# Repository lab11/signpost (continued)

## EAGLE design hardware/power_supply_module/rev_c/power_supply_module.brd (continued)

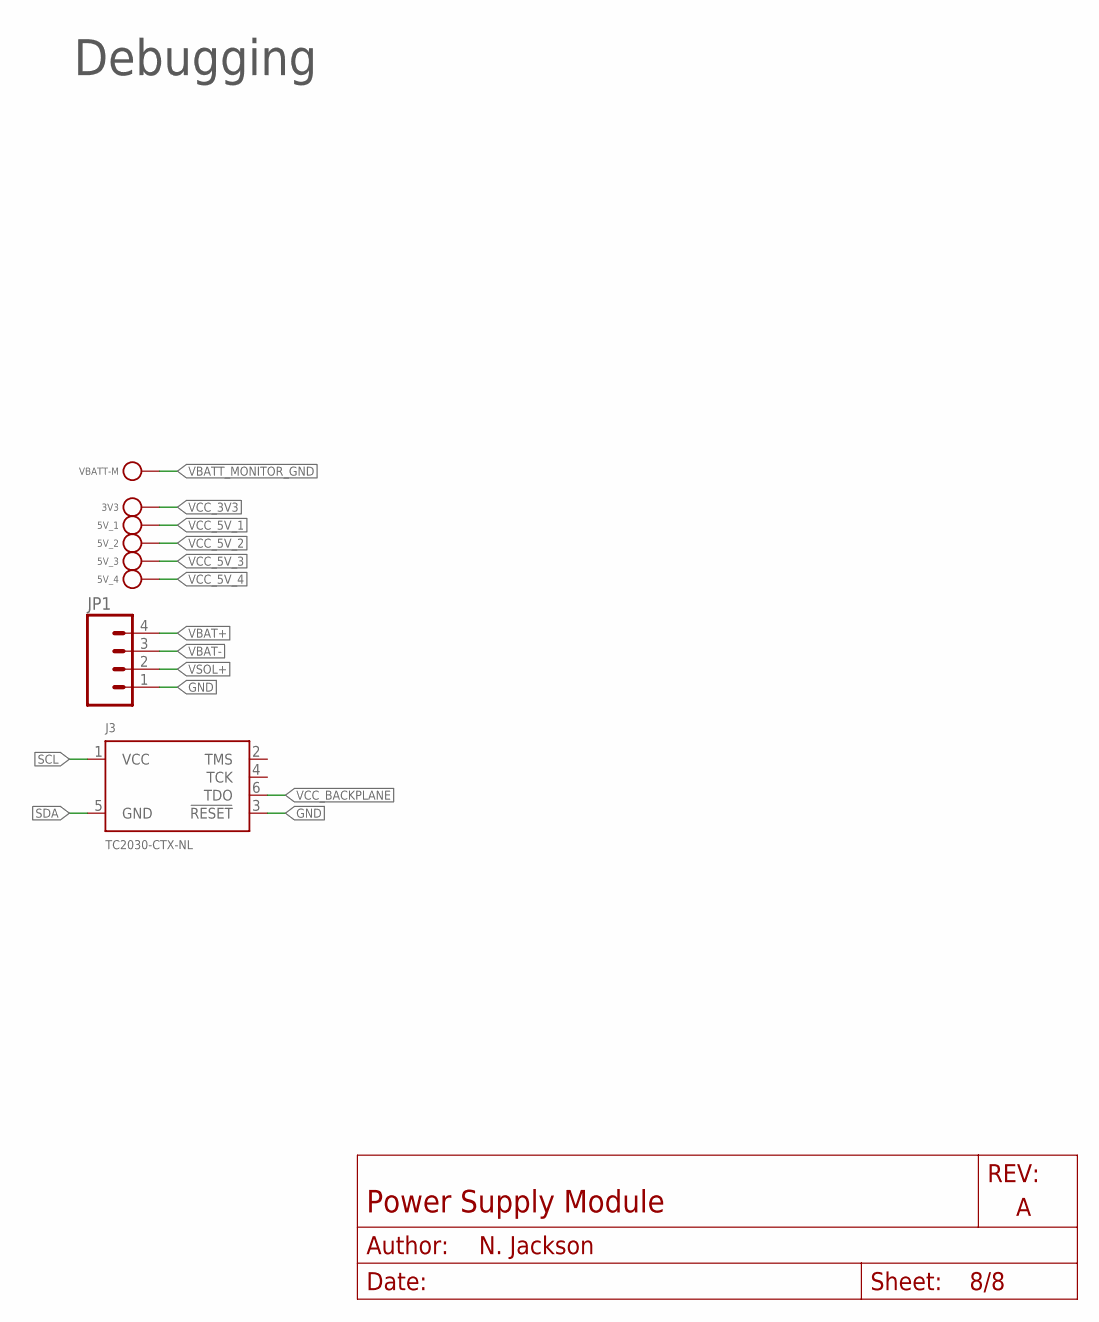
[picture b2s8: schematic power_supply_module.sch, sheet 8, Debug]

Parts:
3V3, 5V_1, 5V_2, 5V_3, 5V_4: TEST_POINT_0.040IN; TESTPOINT_0.040IN
J3: TC2030-CTX-NL; TC2030-IDC-NL
JP1: M04PTH; 1X04
VBATT-M: TEST_POINT_0.040IN; TESTPOINT_0.040IN

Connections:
GND: J3.3 (!RESET), JP1.1; also elsewhere on the board
SCL: J3.1 (VCC); also elsewhere on the board
SDA: J3.5 (GND); also elsewhere on the board
VBAT+: JP1.4; also elsewhere on the board
VBAT-: JP1.3; also elsewhere on the board
VBATT_MONITOR_GND: VBATT-M.TESTPOINT; also elsewhere on the board
VCC_3V3: 3V3.TESTPOINT; also elsewhere on the board
VCC_5V_1: 5V_1.TESTPOINT; also elsewhere on the board
VCC_5V_2: 5V_2.TESTPOINT; also elsewhere on the board
VCC_5V_3: 5V_3.TESTPOINT; also elsewhere on the board
VCC_5V_4: 5V_4.TESTPOINT; also elsewhere on the board
VCC_BACKPLANE: J3.6 (TDO); also elsewhere on the board
VSOL+: JP1.2; also elsewhere on the board

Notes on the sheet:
Debugging

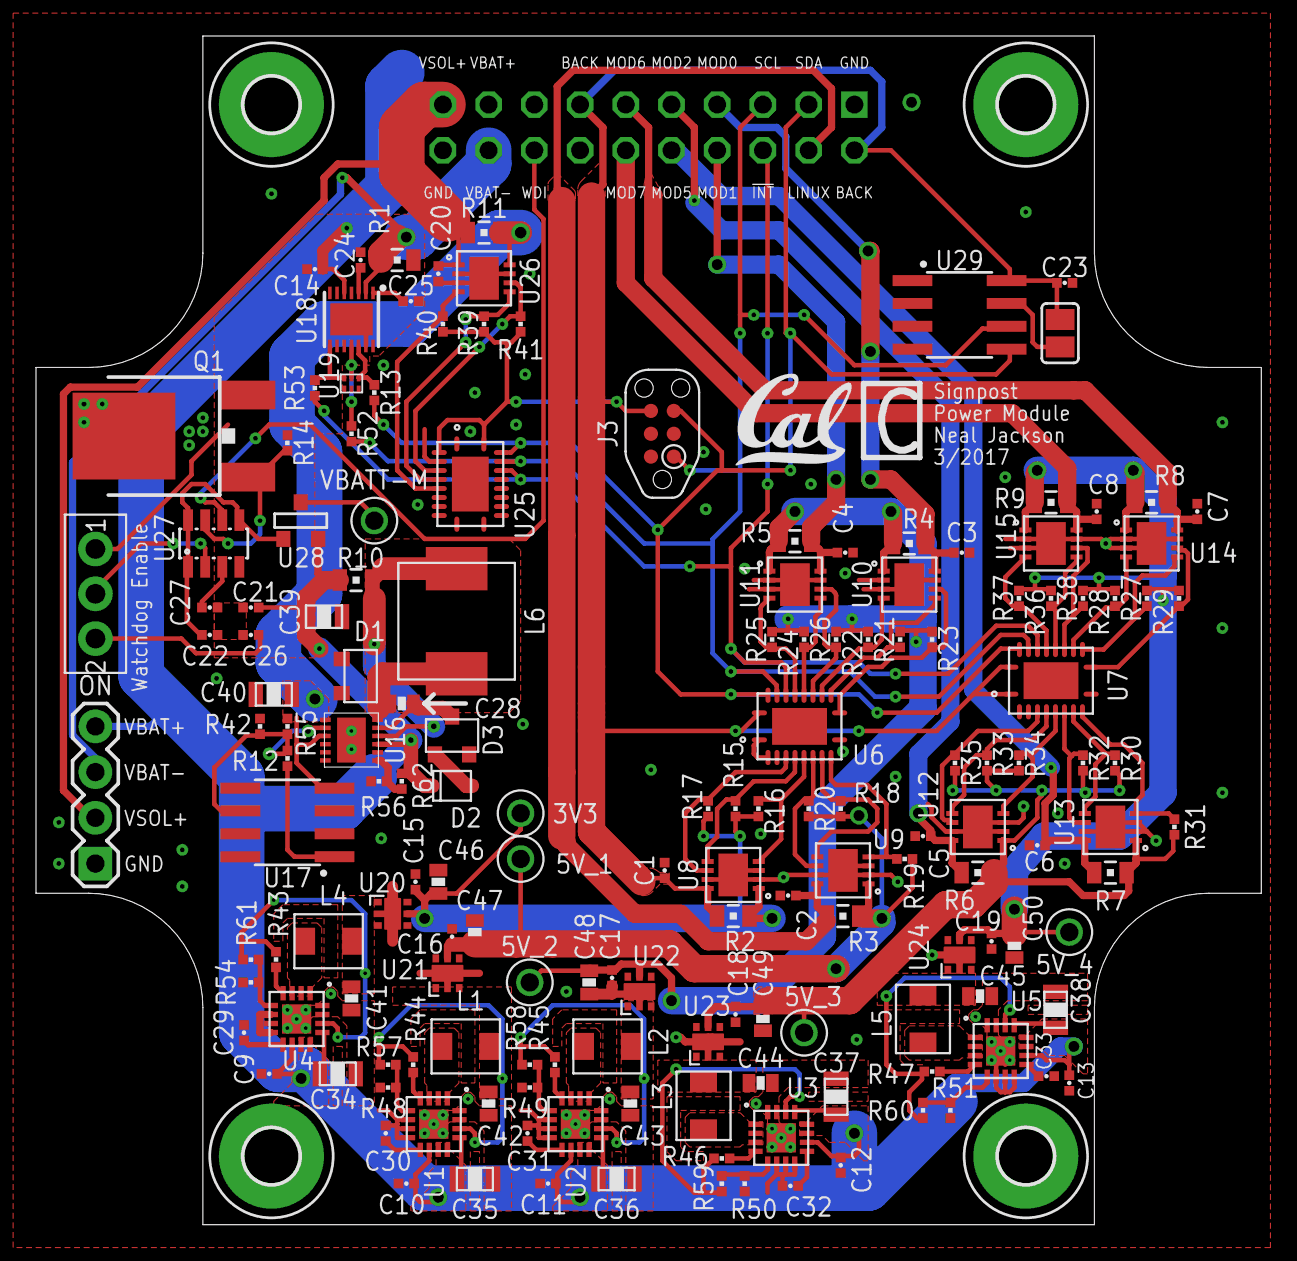
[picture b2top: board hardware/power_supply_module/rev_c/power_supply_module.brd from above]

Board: 2 copper layers, 68.1 x 66.0 mm, 167 parts (0 on the bottom side), 93 nets.

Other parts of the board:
U$1: UCB_CAL_200MIL

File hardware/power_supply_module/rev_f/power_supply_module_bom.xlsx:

Qty | Value | Device | Package | Parts | Description | DESCRIPTION | DIGIKEY | MANUFACTURER | MOUSER | MPN
1 |  | DIODE_SCHOTTKYSOD323 | SOD323 | D3 |  | DIODE SCHOTTKY 40V 200MA SOD323 | CMDSH2-4L CT-ND | Central Semiconductor |  | CMDSH2-4L TR
1 | 0.010 Ω | RESISTOR0805_RES | 0805_RES | R1 | Resistor | RES SMD 0.01 OHM 1% 1/2W 0805 | WSLPB-.01CT-ND | Vishay Dale |  | WSLP0805R0100FEB
8 | 0.017 Ω | RESISTOR0805_RES | 0805_RES | R2, R3, R4, R5, R6, R7, R8, R9 | Resistor | RES SMD 0.017 OHM 1% 1/2W 0805 | WSLPB-.017CT-ND | Vishay Dale |  | WSLP0805R0170FEB
2 | 0.05 Ω | RESISTOR0805_RES | 0805_RES | R10, R11 | Resistor | RES SMD 0.05 OHM 1% 1/2W 0805 | WSLPB-.05CT-ND | Vishay Dale |  | WSLP0805R0500FEB
23 | 0.1 uF | CAPACITOR0402_CAP | 0402_CAP | C1, C2, C3, C4, C5, C6, C7, C8, C9, C10, C11, C12, C13, C14, C15, C16, C17, C18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 | SMD Capacitor | CAP CER 0.1UF 25V X5R 0402 | 490-5920-1-ND | Murata |  | GRM155R61E104KA87D
3 | 0.47 uF | CAPACITOR0402_CAP | 0402_CAP | C24, C25, C26 | SMD Capacitor | CAP CER 0.47UF 6.3V X5R 0402 | 490-3266-1-ND | Murata |  | GRM155R60J474KE19D
1 | 0.82 uF | CAPACITOR0402_CAP | 0402_CAP | C27 | SMD Capacitor | CAP CER 0.82UF 6.3V X6S 0402 | 490-10440-1-ND | Murata |  | GRM155C80J824KE15D
2 | 1 MΩ | RESISTOR0402_RES | 0402_RES | R15, R16 | Resistor | RES SMD 1M OHM 1% 1/10W 0402 | P1.00MLCT-ND | Panasonic |  | ERJ-2RKF1004X
3 | 1 kΩ | RESISTOR0402_RES | 0402_RES | R12, R13, R66 | Resistor | RES SMD 1K OHM 5% 1/10W 0402 | P1.0KJCT-ND | Panasonic |  | ERJ-2GEJ102X
1 | 1 uF | CAPACITOR0603_CAP | 0603_CAP | C28 | SMD Capacitor | CAP CER 1UF 10V X5R 0603 | 490-1543-1-ND | Murata |  | GRM188R61A105KA61D
7 | 10 uF | CAPACITOR0805_CAP | 0805_CAP | C34, C35, C36, C37, C38, C39, C40 | SMD Capacitor | CAP CER 10UF 25V 10% X5R 0805 | 490-5523-1-ND | Murata |  | GRM21BR61E106KA73L
5 | 100 kΩ | RESISTOR0402_RES | 0402_RES | R45, R46, R47, R48, R49 | Resistor | RES SMD 100K OHM 5% 1/10W 0402 | P100KJCT-ND | Panasonic |  | ERJ-2GEJ104X
4 | 130 kΩ | RESISTOR0402_RES | 0402_RES | R50, R51, R52, R53 | Resistor | RES SMD 130K OHM 1% 1/10W 0402 | P130KLCT-ND | Panasonic |  | ERJ-2RKF1303X
3 | 150 Ω | RESISTOR0402_RES | 0402_RES | R54, R55, R70 | Resistor | RES SMD 150 OHM 1% 1/10W 0402 | P150LCT-ND | Panasonic |  | ERJ-2RKF1500X
27 | 2 kΩ | RESISTOR0402_RES | 0402_RES | R17, R18, R19, R20, R21, R22, R23, R24, R25, R26, R27, R28, R29, R30, R31, R32,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 | Resistor | RES SMD 2K OHM 1% 1/10W 0402 | P2.00KLCT-ND | Panasonic |  | ERJ-2RKF2001X
5 | 2.2 uH | INDUCTORIHL | IHL-1212BZ-11 | L1, L2, L3, L4, L5 | A very specific inductor |  | 541-1322-1-ND | Vishay Dale |  | IHLP1212BZER2R2M11
10 | 22 uF | CAPACITOR0603_CAP | 0603_CAP | C41, C42, C43, C44, C45, C46, C47, C48, C49, C50 | SMD Capacitor | CAP CER 22UF 6.3V X5R 0603 | 1276-1193-1-ND | Samsung |  | CL10A226MQ8NRNC
1 | 23.2 kΩ | RESISTOR0805_RES | 0805_RES | R44 | Resistor | RES SMD 23.2K OHM 0.1% 1/8W 0805 | P23.2KDACT-ND | Panasonic |  | ERA6AEB2322V
1 | 240 kΩ | RESISTOR0402_RES | 0402_RES | R56 | Resistor | RES SMD 240K OHM 1% 1/10W 0402 | P240KLCT-ND | Panasonic |  | ERJ-2RKF2403X
5 | 3.3 nF | CAPACITOR0402_CAP | 0402_CAP | C29, C30, C31, C32, C33 | SMD Capacitor | CAP CER 3300PF 50V 10% X7R 0402 | 490-3248-1-ND | Murata |  | GRM155R71H332KA01D
1 | 3.3V | TILM34803.3V | SOT-23 | U28 | Very simple LDO 100ma 3v3 | IC REG LDO 3.3V 50MA SOT23-3 | ZMR330FCT-ND | Diodes Inc. |  | ZMR330FTA
1 | 301 kΩ | RESISTOR0805_RES | 0805_RES | R57 | Resistor | RES SMD 301K OHM 0.1% 1/8W 0805 | P301KDACT-ND | Panasonic |  | ERA-6AEB3013V
1 | 340 kΩ | RESISTOR0805_RES | 0805_RES | R58 | Resistor | RES SMD 340K OHM 0.1% 1/8W 0805 | P340KDACT-ND | Panasonic |  | ERA-6AEB3403V
1 | 6.8uH | INDUCTORIHL2525CZ | IHL-2525CZ | L6 | A very specific inductor | FIXED IND 6.8UH 5.5A 46.8 MOHM | 541-2582-1-ND | Vishay Dale |  | IHLP2525CZER6R8M11
4 | 680 kΩ | RESISTOR0402_RES | 0402_RES | R59, R60, R61, R62 | Resistor | RES SMD 680K OHM 1% 1/10W 0402 | P680KLCT-ND | Panasonic |  | ERJ-2RKF6803X
1 | 750 kΩ | RESISTOR0402_RES | 0402_RES | R63 | Resistor | RES SMD 750K OHM 5% 1/10W 0402 | P750KJCT-ND | Panasonic |  | ERJ-2GEJ754X
1 | 953 kΩ | RESISTOR0805_RES | 0805_RES | R64 | Resistor | RES SMD 953K OHM 0.1% 1/8W 0805 | P953KDACT-ND | Panasonic |  | ERA-6AEB9533V
5 | AP22814 | AP22814 | U-DFN2020-6 | U20, U21, U22, U23, U24 | SINGLE CHANNEL POWER DISTRIBUTION LOAD SWITCH |  | AP22814ASN-7DICT-ND | Diodes Inc. |  | AP22814ASN-7
1 | DIODE_SCHOTTKYSOT-23F | DIODE_SCHOTTKYSOT-23F | SOT-23F | D1 |  | DIODE SCHOTTKY 40V 1.75A SOT23F | CMPSH1-4 CT-ND | Central Semiconductor |  | CMPSH1-4 TR
1 | DIODE_ZENERSOT323 | DIODE_ZENERSOT323 | SOD323 | D2 |  | DIODE ZENER 3.6V 400MW SOD323 | 1727-5151-1-ND | NXP Semiconductors |  | PDZ3.6B,115
1 | ESDR0502N | ESDR0502N | UDFN-6 | U19 |  |  | ESDR0502NMUTBGOSCT-ND | ON Semiconductor |  | ESDR0502NMUTBG
1 | LM234 | LM234 | SOIC-8 | U17 | 3-terminal temperature sensor |  | 497-1549-1-ND | STMicroelectronics |  | LM234DT
1 | LT3652 | LT3652 | DFN-12/3MM | U16 | Solar power tracking 2A battery charger |  | LT3652EDD#PBF-ND | Linear Technology |  | LT3652EDD#PBF
1 | LTC2941 | LTC2941 | DFN-6-2MMX3MM | U8 | I2C Battery Gas Gauge |  | LTC2941IDCB#TRMPBFCT-ND | Linear Technology |  | LTC2941IDCB#TRMPBF
8 | LTC2943 | LTC2943 | DFN-8 | U9, U10, U11, U12, U13, U14, U15, U26 | Multicell Battery Gas Gauge |  | LTC2943IDD#PBF-ND | Linear Technology |  | LTC2943IDD#PBF
1 | M24C01WMN | M24C01WMN | SOIC-8 | U29 | 1K I2C™ Serial EEPROM |  | 497-8631-1-ND | STMicroelectronics |  | M24C01-WMN6TP
1 | MAX17205 | MAX17205 | 14-TDFN | U18 | Stand-Alone ModelGauge m5 Fuel Gauge |  | MAX17205G+00E-ND | Maxim Integrated | 700-MAX17205G+00E | MAX17205G+00E
1 | MAX6746 | MAX6746 | SOT-23-8 | U27 | A simple watchdog timer with adjustable timeouts and reset time |  | MAX6746KA29+TCT-ND | Maxim Integrated |  | MAX6746KA29+T
1 | MODULE_POWER | MODULE_POWER | MODULE_POWER | J1 | Header for power module for signpost |  | S9172-ND | Sullins Connector Solutions |  | SBH11-PBPC-D10-ST-BK
1 | MOSFET-NCHANNELSMD | MOSFET-NCHANNELSMD | SOT23-3 | Q1 | Generic NMOS footprint | MOSFET N-CH 60V 0.115A SOT-23 | 2N7002LT1GOSCT-ND | ON Semiconductor |  | 2N7002LT1G
3 | PCA9544AQFN-N20 | PCA9544AQFN-N20 | QFN-N20 | U6, U7, U25 | 1-4 I2C/SMBUS Multiplexer with interrupt for power supply coulomb counters |  | 296-20960-1-ND | Texas Instruments |  | PCA9544ARGYR
1 | PTS810SJ | PTS810SJ | PTS810SJ | S2 | PTS810SJ Push Button Switch |  | CKN10504CT-ND | C&K |  | PTS810 SJG 250 SMTR LFS
1 | SN74AUP1T14DCKR | SN74AUP1T14DCKR | SC70 | U30 | LOW POWER, 1.8/2.5/3.3-V INPUT, 3.3-V CMOS OUTPUT, SINGLE |  | 296-27392-1-ND | Texas Instruments |  | SN74AUP1T14DCKR
1 | TE_SSA12/SPDT | TE_SSA12/SPDT | TE_SSA12/SPDT | S1 | SWITCH SLIDE SPDT 2POS SSA SER |  | 450-1602-ND | TE Connectivity |  | SSA12
5 | TLV62130 | TLV62130 | TQFN-16/3MM | U1, U2, U3, U4, U5 | High Efficient 3A switching step-down regulator. 1V-5V out, 4V-17V in. |  | 296-35978-1-ND | Texas Instruments |  | TLV62130RGTR

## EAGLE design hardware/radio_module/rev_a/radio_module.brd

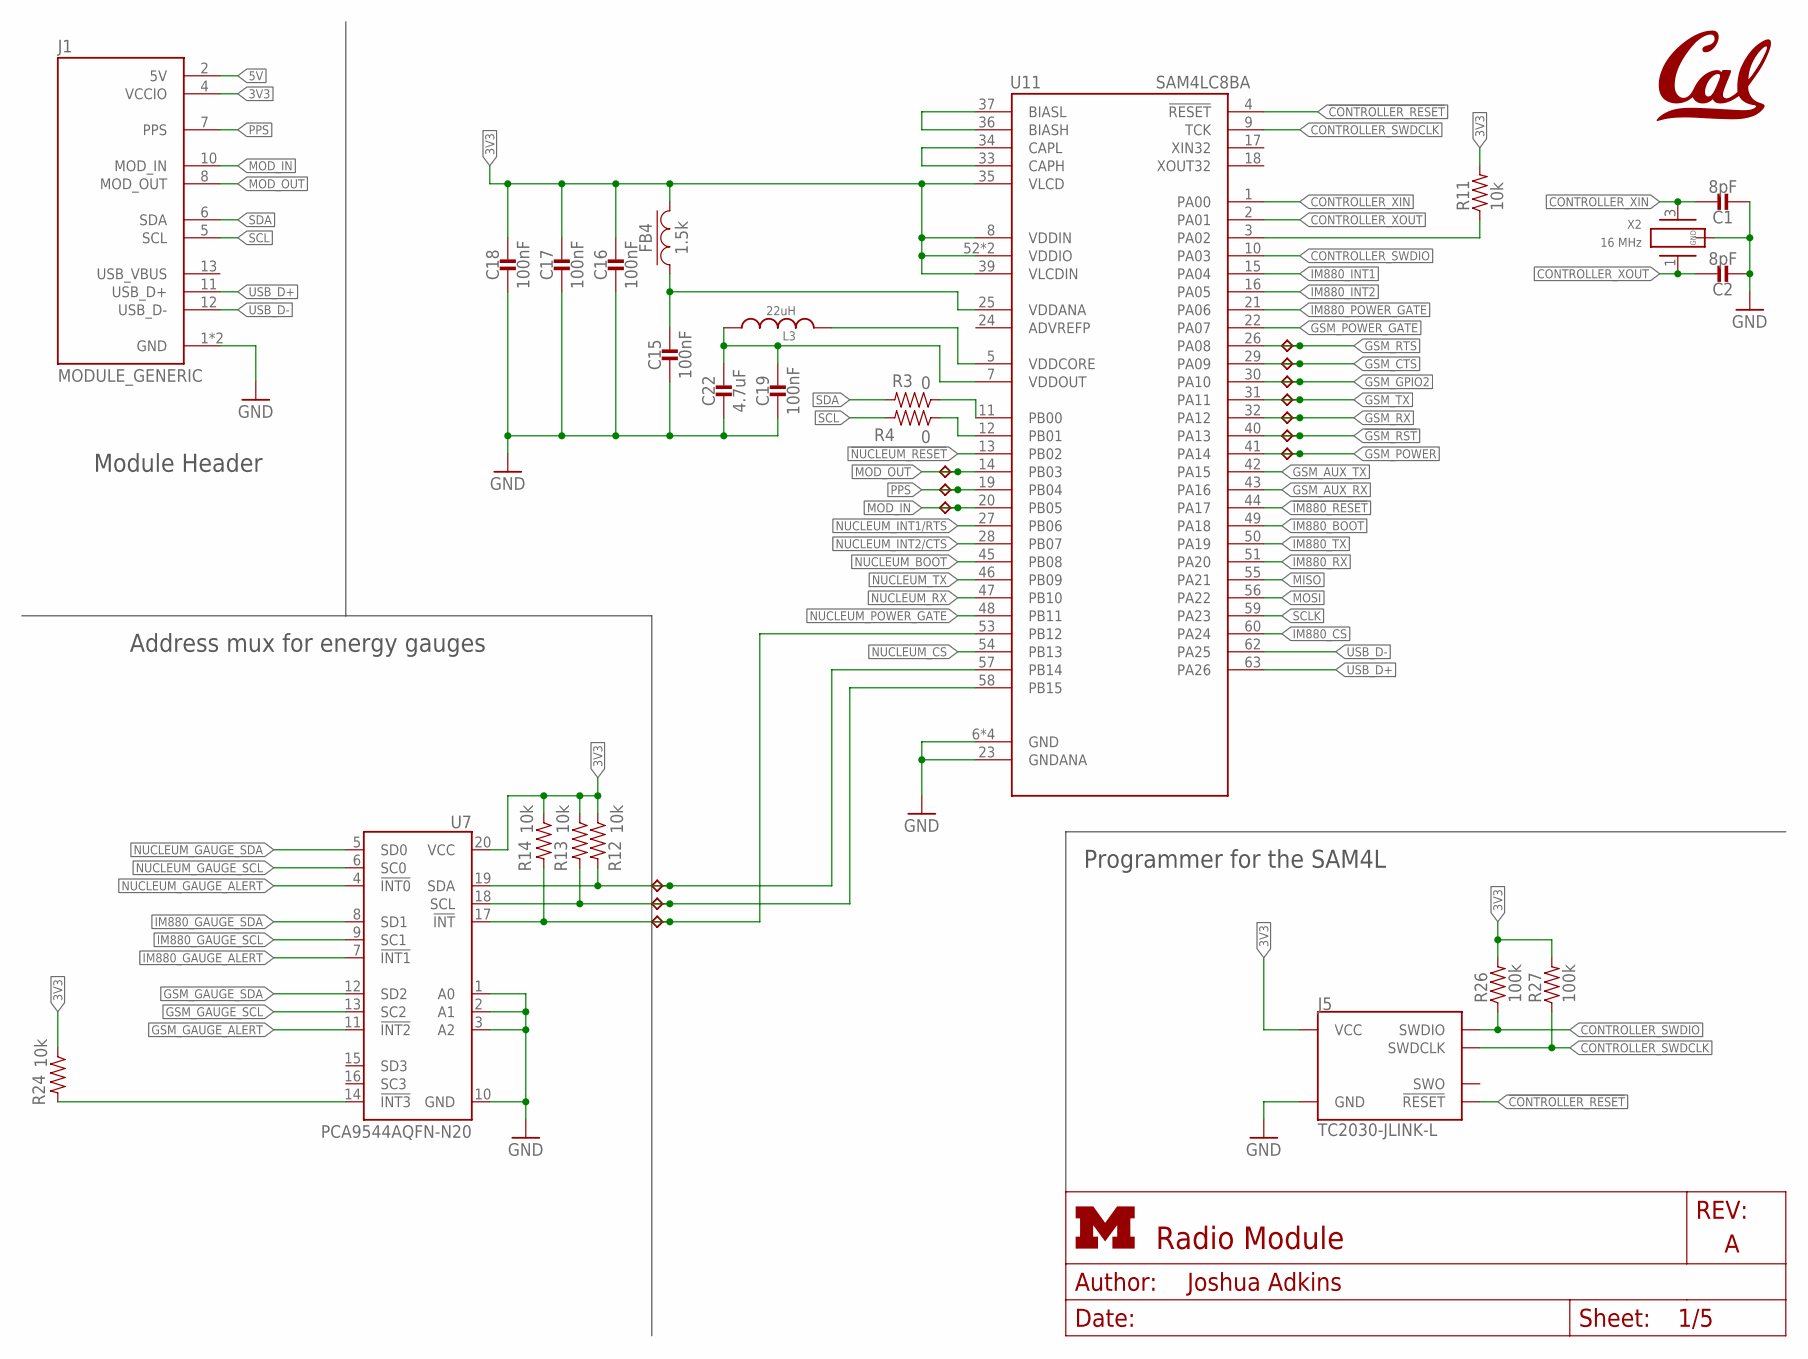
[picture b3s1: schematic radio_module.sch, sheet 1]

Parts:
C1, C2: 8pF; 0402_CAP; DIGIKEY 490-8230-1-ND
C15, C16, C17, C18, C19: 100nF; 0402_CAP; DIGIKEY 490-10777-1-ND
C22: 4.7uF; 0402_CAP; DIGIKEY 490-13252-1-ND
FB4: 1.5k; 0402_CAP; DIGIKEY 490-5216-1-ND
J1: MODULE_GENERIC
J5: TC2030-JLINK-L; TC2030-IDC
L3: 22uH; 1212
R3, R4: 0; 0402_RES; DIGIKEY 1276-3431-1-ND
R11, R12, R13, R14, R24: 10k; 0402_RES; DIGIKEY 1276-3431-1-ND
R26, R27: 100k; 0402_RES; DIGIKEY 1276-3432-1-ND
TP1, TP2, TP3, TP4, TP5, TP6, TP7, TP8, TP9, TP10, TP11, TP12, TP13: TPB1,27; B1,27
U7: PCA9544AQFN-N20; QFN-N20
U11: SAM4LC8BA; QFN-64-9MM
U$1: UCB_CAL100MIL; UCB_CAL_100MIL
X2: 16 MHz; FHXXX

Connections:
3V3: C16.1, C17.1, C18.1, FB4.2, J1.4 (VCCIO), J5.1 (VCC), R11.2, R12.1, R13.1, R14.1, R24.1, R26.2, R27.2, U7.20 (VCC), U11.8 (VDDIN), U11.35 (VLCD), U11.39 (VLCDIN), U11.52 (VDDIO), U11.61 (VDDIO); also elsewhere on the board
5V: J1.2 (5V); also elsewhere on the board
!CONTROLLER_RESET: J5.3 (!RESET), U11.4 (!RESET)
!GSM_RST: TP7.TP, U11.40 (PA13); also elsewhere on the board
!IM880_RESET: U11.44 (PA17); also elsewhere on the board
!NUCLEUM_RESET: U11.13 (PB02); also elsewhere on the board
ADVREFP: U11.24 (ADVREFP)
CONTROLLER_BUCK/LDO_N: R11.1, U11.3 (PA02)
CONTROLLER_SWDCLK: J5.4 (SWDCLK), R27.1, U11.9 (TCK)
CONTROLLER_SWDIO: J5.2 (SWDIO), R26.1, U11.10 (PA03)
CONTROLLER_XIN: C1.1, U11.1 (PA00), X2.3 (2)
CONTROLLER_XOUT: C2.1, U11.2 (PA01), X2.1
GND: C1.2, C2.2, C15.2, C16.2, C17.2, C18.2, C19.2, C22.2, J1.1 (GND), J1.14 (GND), J5.5 (GND), U7.1 (A0), U7.2 (A1), U7.3 (A2), U7.10 (GND), U11.6 (GND), U11.23 (GNDANA), U11.38 (GND), U11.64 (GND), U11.GND, X2.2 (GND), X2.4 (GND); also elsewhere on the board
GSM_AUX_RX: U11.43 (PA16); also elsewhere on the board
GSM_AUX_TX: U11.42 (PA15); also elsewhere on the board
GSM_CTS: TP11.TP, U11.29 (PA09); also elsewhere on the board
GSM_GAUGE_ALERT: U7.11 (!INT2); also elsewhere on the board
GSM_GAUGE_SCL: U7.13 (SC2); also elsewhere on the board
GSM_GAUGE_SDA: U7.12 (SD2); also elsewhere on the board
GSM_GPIO2: TP10.TP, U11.30 (PA10); also elsewhere on the board
GSM_POWER: TP6.TP, U11.41 (PA14); also elsewhere on the board
GSM_POWER_GATE: U11.22 (PA07); also elsewhere on the board
GSM_RTS: TP12.TP, U11.26 (PA08); also elsewhere on the board
GSM_RX: TP8.TP, U11.32 (PA12); also elsewhere on the board
GSM_TX: TP9.TP, U11.31 (PA11); also elsewhere on the board
IM880_BOOT: U11.49 (PA18); also elsewhere on the board
IM880_CS: U11.60 (PA24); also elsewhere on the board
IM880_GAUGE_ALERT: U7.7 (!INT1); also elsewhere on the board
IM880_GAUGE_SCL: U7.9 (SC1); also elsewhere on the board
IM880_GAUGE_SDA: U7.8 (SD1); also elsewhere on the board
IM880_INT1: U11.15 (PA04); also elsewhere on the board
IM880_INT2: U11.16 (PA05); also elsewhere on the board
IM880_POWER_GATE: U11.21 (PA06); also elsewhere on the board
IM880_RX: U11.51 (PA20); also elsewhere on the board
IM880_TX: U11.50 (PA19); also elsewhere on the board
MISO: U11.55 (PA21); also elsewhere on the board
MOD_IN: J1.10 (MOD_IN), TP3.TP, U11.20 (PB05)
MOD_OUT: J1.8 (MOD_OUT), TP1.TP, U11.14 (PB03)
MOSI: U11.56 (PA22); also elsewhere on the board
unnamed: R14.2, TP13.TP, U7.17 (!INT), U11.53 (PB12)
unnamed: R24.2, U7.14 (!INT3)
unnamed: R3.1, U11.11 (PB00)
unnamed: R4.1, U11.12 (PB01)
unnamed: C15.1, FB4.1, U11.25 (VDDANA)
unnamed: C19.1, C22.1, L3.P$1 (1), U11.7 (VDDOUT)
unnamed: L3.P$2 (2), U11.5 (VDDCORE)
unnamed: U11.36 (BIASH), U11.37 (BIASL)
unnamed: U11.33 (CAPH), U11.34 (CAPL)
NUCLEUM_BOOT: U11.45 (PB08); also elsewhere on the board
NUCLEUM_CS: U11.54 (PB13); also elsewhere on the board
NUCLEUM_GAUGE_ALERT: U7.4 (!INT0); also elsewhere on the board
NUCLEUM_GAUGE_SCL: U7.6 (SC0); also elsewhere on the board
NUCLEUM_GAUGE_SDA: U7.5 (SD0); also elsewhere on the board
NUCLEUM_INT1/RTS: U11.27 (PB06); also elsewhere on the board
NUCLEUM_INT2/CTS: U11.28 (PB07); also elsewhere on the board
NUCLEUM_POWER_GATE: U11.48 (PB11); also elsewhere on the board
NUCLEUM_RX: U11.47 (PB10); also elsewhere on the board
NUCLEUM_TX: U11.46 (PB09); also elsewhere on the board
PPS: J1.7 (PPS), TP2.TP, U11.19 (PB04)
SCL: J1.5 (SCL), R4.2; also elsewhere on the board
SCLK: U11.59 (PA23); also elsewhere on the board
SCL_INTERNAL: R13.2, TP5.TP, U7.18 (SCL), U11.58 (PB15)
SDA: J1.6 (SDA), R3.2; also elsewhere on the board
SDA_INTERNAL: R12.2, TP4.TP, U7.19 (SDA), U11.57 (PB14)
USB_D+: J1.11 (USB_D+), U11.63 (PA26)
USB_D-: J1.12 (USB_D-), U11.62 (PA25)

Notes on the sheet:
Module Header
Address mux for energy gauges
Programmer for the SAM4L

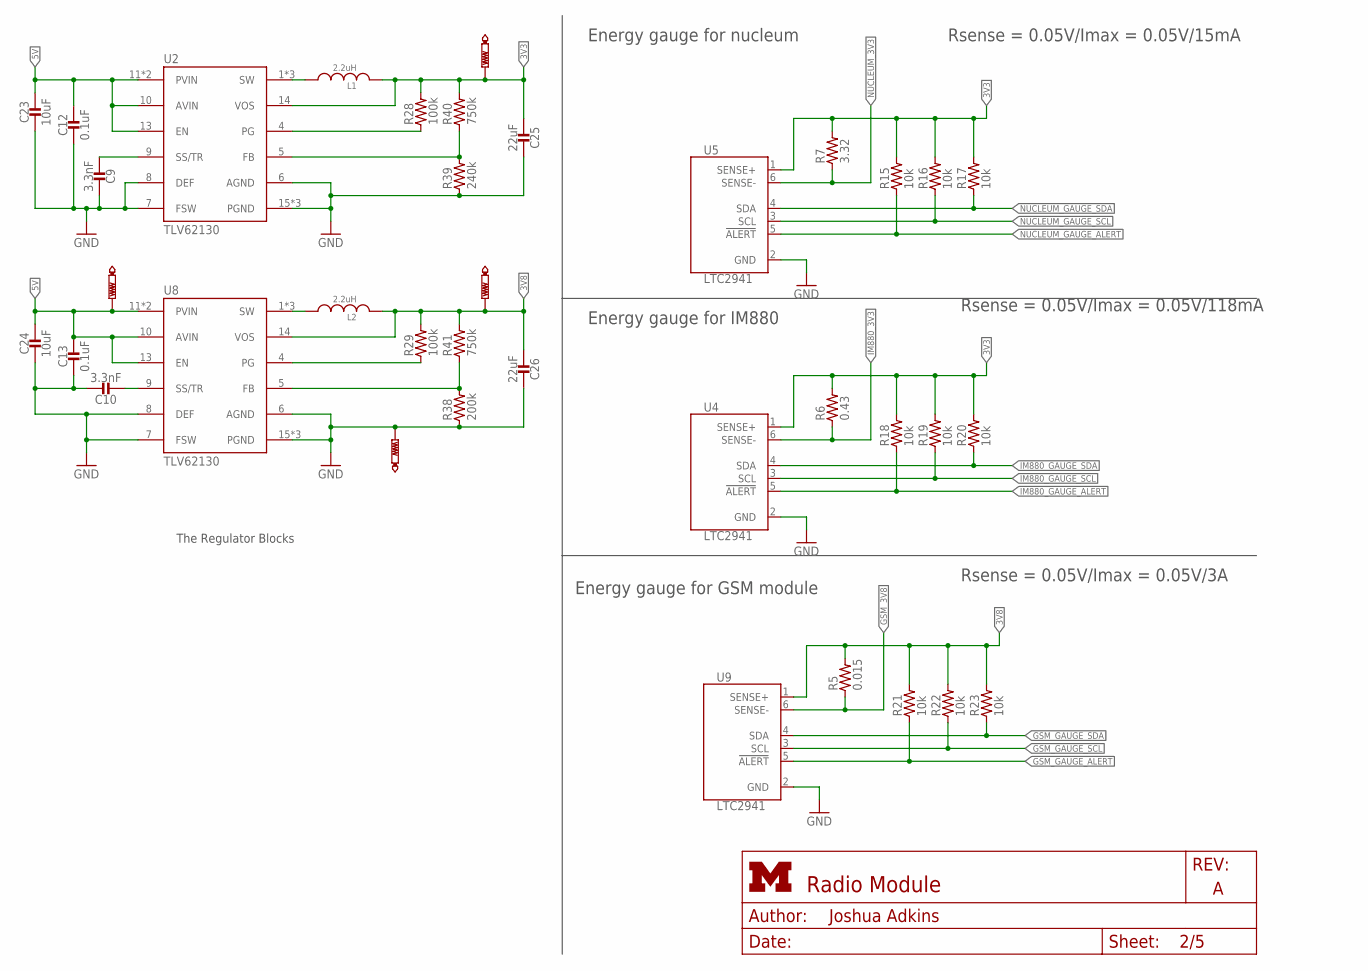
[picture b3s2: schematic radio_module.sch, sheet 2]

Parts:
C9, C10: 3.3nF; 0402_CAP
C12, C13: 0.1uF; 0402_CAP
C23, C24: 10uF; 0402_CAP
C25, C26: 22uF; 0402_CAP
L1, L2: 2.2uH; IHL-1212BZ-11
R5: 0.015; 0603-RES
R6: 0.43; 0402_RES
R7: 3.32; 0402_RES
R15, R16, R17, R18, R19, R20, R21, R22, R23: 10k; 0402_RES
R28, R29: 100k; 0402_RES
R38: 200k; 0402_RES
R39: 240k; 0402_RES
R40, R41: 750k; 0402_RES
TP14, TP15, TP16, TP17: PTR1PAD1-13; P1-13
U2, U8: TLV62130; TQFN-16/3MM
U4, U5, U9: LTC2941; DFN-6-2MMX3MM

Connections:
3V3: C25.2, L1.P$2 (2), R6.2, R7.2, R15.2, R16.2, R17.2, R18.2, R19.2, R20.2, R28.2, R40.2, TP17.TP, U2.14 (VOS), U4.1 (SENSE+), U5.1 (SENSE+); also elsewhere on the board
3V8: C26.2, L2.P$2 (2), R5.2, R21.2, R22.2, R23.2, R29.2, R41.2, TP14.TP, U8.14 (VOS), U9.1 (SENSE+)
3V8SWOUT: L2.P$1 (1), U8.1 (SW), U8.2 (SW), U8.3 (SW)
3VSWOUT: L1.P$1 (1), U2.1 (SW), U2.2 (SW), U2.3 (SW)
5V: C12.1, C13.1, C23.1, C24.1, TP16.TP, U2.10 (AVIN), U2.11 (PVIN), U2.12 (PVIN), U2.13 (EN), U8.10 (AVIN), U8.11 (PVIN), U8.12 (PVIN), U8.13 (EN); also elsewhere on the board
GND: C9.1, C10.1, C12.2, C13.2, C23.2, C24.2, C25.1, C26.1, R38.1, R39.1, TP15.TP, U2.6 (AGND), U2.7 (FSW), U2.8 (DEF), U2.15 (PGND), U2.16 (PGND), U2.GND, U4.2 (GND), U5.2 (GND), U8.6 (AGND), U8.7 (FSW), U8.8 (DEF), U8.15 (PGND), U8.16 (PGND), U8.GND, U9.2 (GND); also elsewhere on the board
GSM_3V8: R5.1, U9.6 (SENSE-); also elsewhere on the board
GSM_GAUGE_ALERT: R21.1, U9.5 (!ALERT); also elsewhere on the board
GSM_GAUGE_SCL: R22.1, U9.3 (SCL); also elsewhere on the board
GSM_GAUGE_SDA: R23.1, U9.4 (SDA); also elsewhere on the board
IM880_3V3: R6.1, U4.6 (SENSE-); also elsewhere on the board
IM880_GAUGE_ALERT: R18.1, U4.5 (!ALERT); also elsewhere on the board
IM880_GAUGE_SCL: R19.1, U4.3 (SCL); also elsewhere on the board
IM880_GAUGE_SDA: R20.1, U4.4 (SDA); also elsewhere on the board
unnamed: C9.2, U2.9 (SS/TR)
unnamed: R28.1, U2.4 (PG)
unnamed: R39.2, R40.1, U2.5 (FB)
unnamed: C10.2, U8.9 (SS/TR)
unnamed: R29.1, U8.4 (PG)
unnamed: R38.2, R41.1, U8.5 (FB)
NUCLEUM_3V3: R7.1, U5.6 (SENSE-); also elsewhere on the board
NUCLEUM_GAUGE_ALERT: R15.1, U5.5 (!ALERT); also elsewhere on the board
NUCLEUM_GAUGE_SCL: R16.1, U5.3 (SCL); also elsewhere on the board
NUCLEUM_GAUGE_SDA: R17.1, U5.4 (SDA); also elsewhere on the board

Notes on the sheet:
The Regulator Blocks
Energy gauge for nucleum
Energy gauge for IM880
Energy gauge for GSM module
Rsense = 0.05V/Imax = 0.05V/15mA
Rsense = 0.05V/Imax = 0.05V/118mA
Rsense = 0.05V/Imax = 0.05V/3A

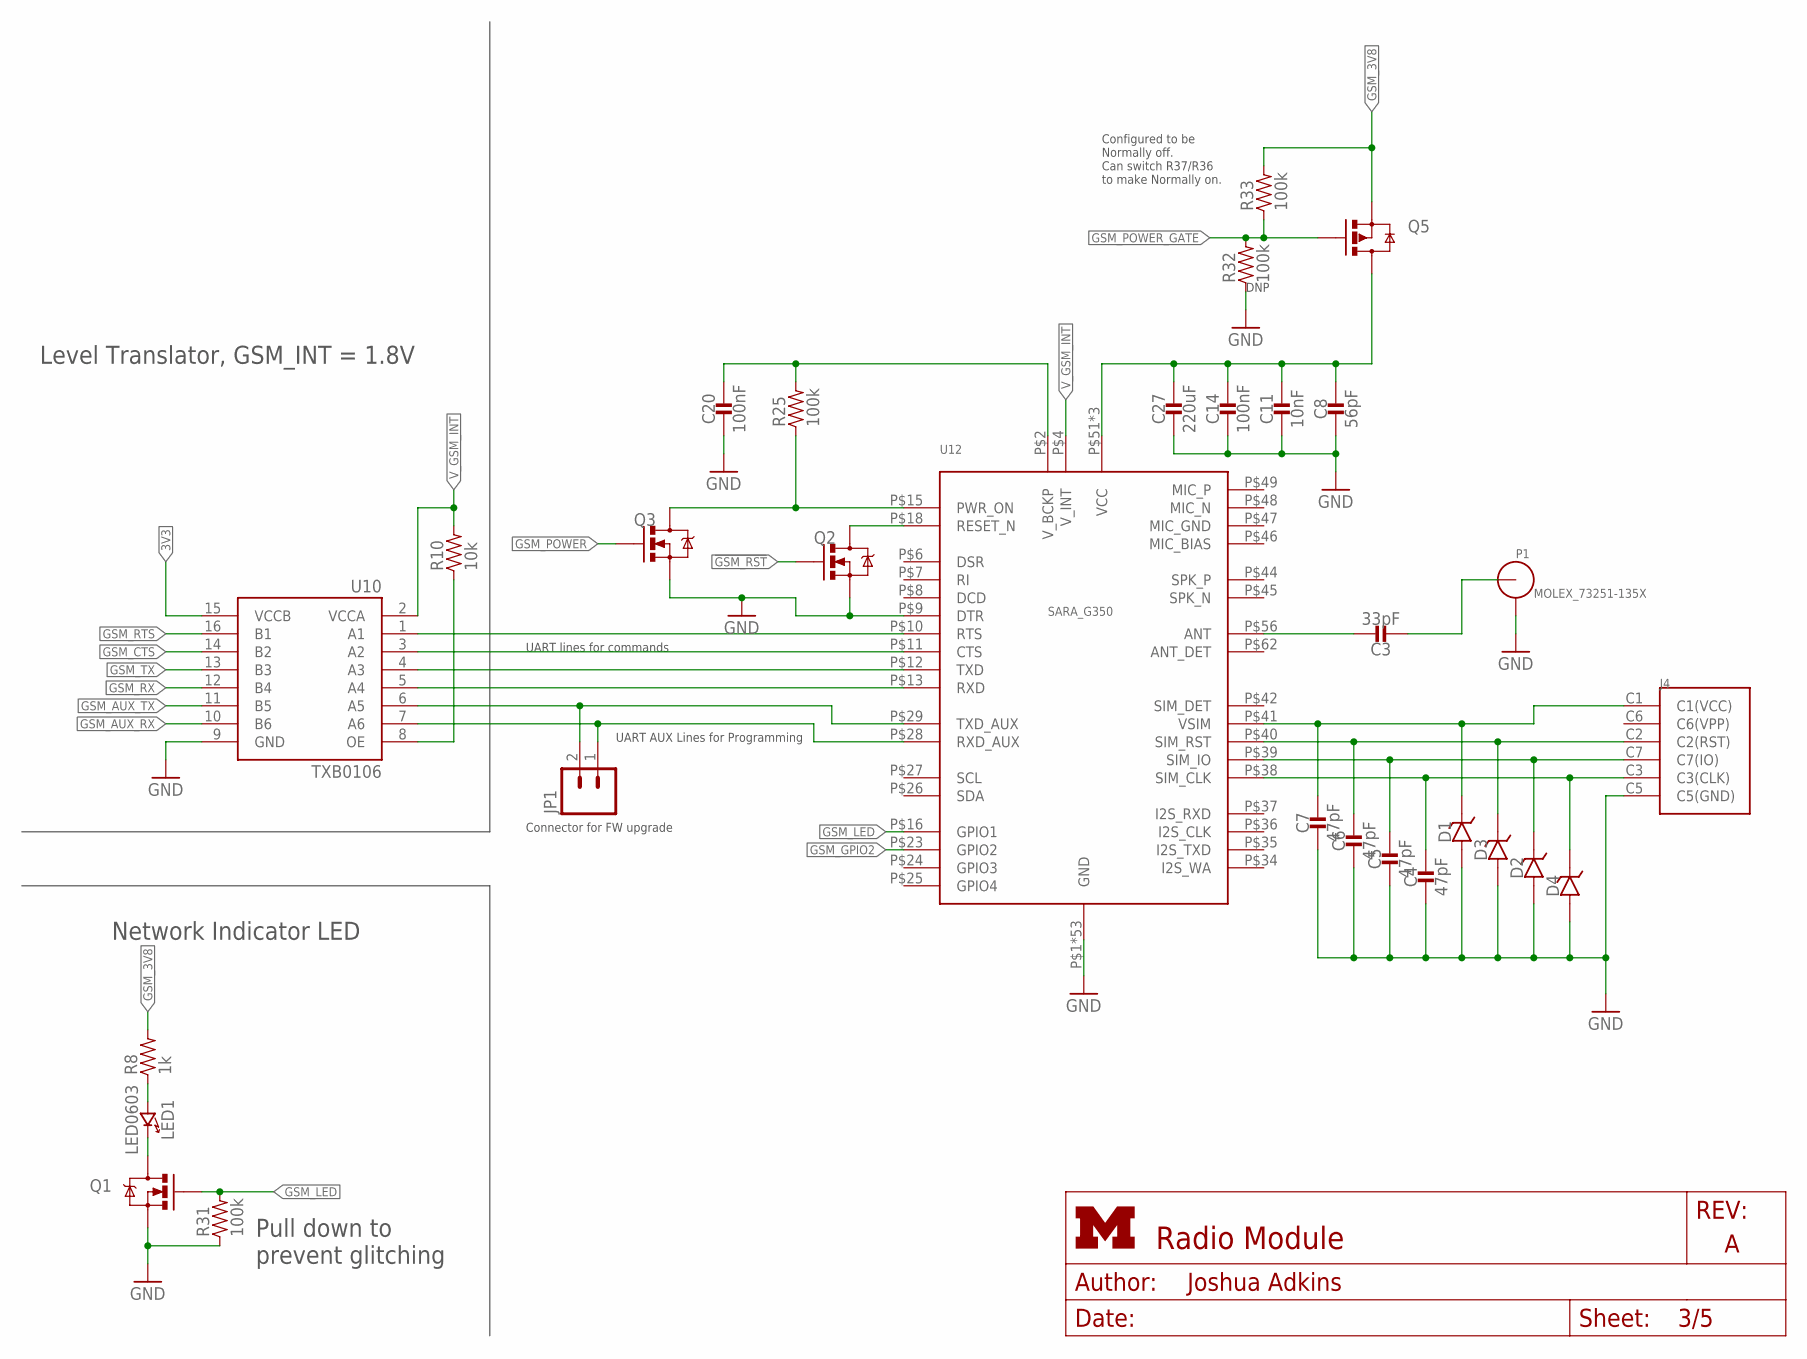
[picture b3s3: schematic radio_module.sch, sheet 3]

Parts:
C3: 33pF; 0603_CAP
C4, C5, C6, C7: 47pF; 0402_CAP
C8: 56pF; 0402_CAP
C11: 10nF; 0402_CAP
C14, C20: 100nF; 0402_CAP
C27: 220uF; 1210_CAP
D1: 14V; 0402_DIODE
D2, D3, D4: DIODE_ZENER; 0402_DIODE
J4: NANO_SIM; WURTH_NANO_SIM
JP1: M02PTH; 1X02
LED1: LED0603; LED-0603
P1: MOLEX_73251-135X; SMA-J/PCB
Q1, Q2, Q3: MOSFET-NCHANNELXFDN-3; XFDFN-3
Q5: SI223DDS; SOT23-3
R8: 1k; 0402_RES
R10: 10k; 0402_RES
R25, R31, R32, R33: 100k; 0402_RES
U10: TXB0106; R-PVQFN-N16
U12: UBLOX_SARA_G350; UBLOX_SARA_G3

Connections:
3V3: U10.15 (VCCB); also elsewhere on the board
!GSM_RST: Q2.G; also elsewhere on the board
GND: C4.2, C5.2, C6.2, C7.2, C8.2, C11.2, C14.2, C20.2, C27.2, D1.ANODE, D2.ANODE, D3.ANODE, D4.ANODE, J4.C5 (C5(GND)), P1.2, P1.3, P1.4, P1.5, Q1.S, Q2.S, Q3.S, R31.1, R32.1, U10.9 (GND), U12.P65 (GND), U12.P66 (GND), U12.P67 (GND), U12.P68 (GND), U12.P69 (GND), U12.P70 (GND), U12.P71 (GND), U12.P72 (GND), U12.P73 (GND), U12.P74 (GND), U12.P75 (GND), U12.P76 (GND), U12.P77 (GND), U12.P78 (GND), U12.P79 (GND), U12.P80 (GND), U12.P81 (GND), U12.P82 (GND), U12.P83 (GND), U12.P84 (GND), U12.P85 (GND), U12.P86 (GND), U12.P87 (GND), U12.P88 (GND), U12.P89 (GND), U12.P90 (GND), U12.P91 (GND), U12.P92 (GND), U12.P93 (GND), U12.P94 (GND), U12.P95 (GND), U12.P96 (GND), U12.P$1 (GND), U12.P$3 (GND), U12.P$5 (GND), U12.P$9 (DTR), U12.P$14 (GND), U12.P$20 (GND), U12.P$21 (GND), U12.P$22 (GND), U12.P$30 (GND), U12.P$32 (GND), U12.P$33 (GND), U12.P$43 (GND), U12.P$50 (GND), U12.P$54 (GND), U12.P$55 (GND), U12.P$57 (GND), U12.P$58 (GND), U12.P$59 (GND), U12.P$60 (GND), U12.P$61 (GND), U12.P$63 (GND), U12.P$64 (GND); also elsewhere on the board
GSM_3V8: Q5.2 (S), R8.2, R33.2; also elsewhere on the board
GSM_AUX_RX: U10.10 (B6); also elsewhere on the board
GSM_AUX_TX: U10.11 (B5); also elsewhere on the board
GSM_CTS: U10.14 (B2); also elsewhere on the board
GSM_GATED: C8.1, C11.1, C14.1, C27.1, Q5.3 (D), U12.P$51 (VCC), U12.P$52 (VCC), U12.P$53 (VCC)
GSM_GPIO2: U12.P$23 (GPIO2); also elsewhere on the board
GSM_LED: Q1.G, R31.2, U12.P$16 (GPIO1)
GSM_POWER: Q3.G; also elsewhere on the board
GSM_POWER_GATE: Q5.1 (G), R32.2, R33.1; also elsewhere on the board
GSM_RTS: U10.16 (B1); also elsewhere on the board
GSM_RX: U10.12 (B4); also elsewhere on the board
GSM_TX: U10.13 (B3); also elsewhere on the board
unnamed: C7.1, D1.CATHODE, J4.C1 (C1(VCC)), U12.P$41 (VSIM)
unnamed: C6.1, D3.CATHODE, J4.C2 (C2(RST)), U12.P$40 (SIM_RST)
unnamed: C5.1, D2.CATHODE, J4.C7 (C7(IO)), U12.P$39 (SIM_IO)
unnamed: C4.1, D4.CATHODE, J4.C3 (C3(CLK)), U12.P$38 (SIM_CLK)
unnamed: R10.1, U10.8 (OE)
unnamed: C3.1, U12.P$56 (ANT)
unnamed: C3.2, P1.1 (ANT)
unnamed: LED1.A (ANODE), R8.1
unnamed: U10.4 (A3), U12.P$12 (TXD)
unnamed: U10.5 (A4), U12.P$13 (RXD)
unnamed: LED1.C (CATHODE), Q1.D
unnamed: Q2.D, U12.P$18 (RESET_N)
unnamed: C20.1, R25.2, U12.P$2 (V_BCKP)
unnamed: Q3.D, R25.1, U12.P$15 (PWR_ON)
unnamed: JP1.2, U10.6 (A5), U12.P$29 (TXD_AUX)
unnamed: JP1.1, U10.7 (A6), U12.P$28 (RXD_AUX)
unnamed: U10.3 (A2), U12.P$11 (CTS)
unnamed: U10.1 (A1), U12.P$10 (RTS)
V_GSM_INT: R10.2, U10.2 (VCCA), U12.P$4 (V_INT)

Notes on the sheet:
Pull down to prevent glitching
Network Indicator LED
Level Translator, GSM_INT = 1.8V
UART AUX Lines for Programming
UART lines for commands
DNP
Configured to be Normally off. Can switch R37/R36 to make Normally on.
Connector for FW upgrade

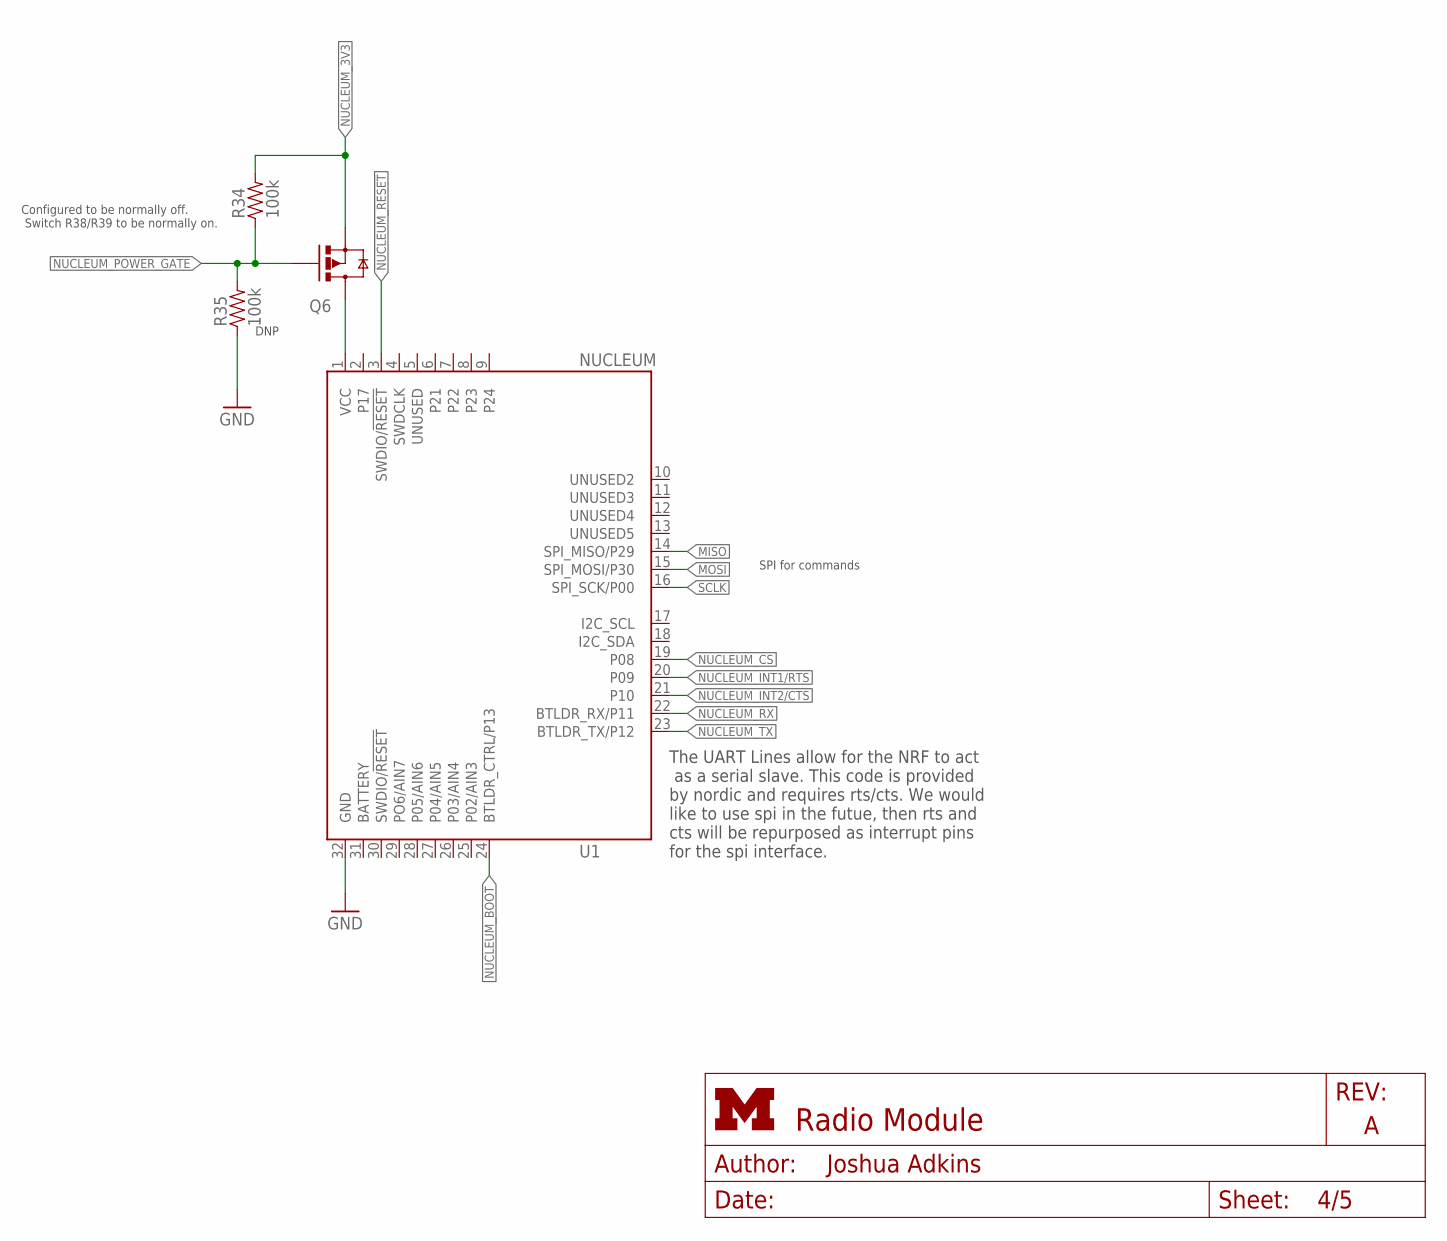
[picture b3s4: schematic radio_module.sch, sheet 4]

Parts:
Q6: SI223DDS; SOT23-3
R34, R35: 100k; 0402_RES
U1: NUCLEUM

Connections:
!NUCLEUM_RESET: U1.3 (SWDIO/!RESET); also elsewhere on the board
GND: R35.1, U1.32 (GND); also elsewhere on the board
MISO: U1.14 (SPI_MISO/P29); also elsewhere on the board
MOSI: U1.15 (SPI_MOSI/P30); also elsewhere on the board
unnamed: Q6.3 (D), U1.1 (VCC)
NUCLEUM_3V3: Q6.2 (S), R34.2; also elsewhere on the board
NUCLEUM_BOOT: U1.24 (BTLDR_CTRL/P13); also elsewhere on the board
NUCLEUM_CS: U1.19 (P08); also elsewhere on the board
NUCLEUM_INT1/RTS: U1.20 (P09); also elsewhere on the board
NUCLEUM_INT2/CTS: U1.21 (P10); also elsewhere on the board
NUCLEUM_POWER_GATE: Q6.1 (G), R34.1, R35.2; also elsewhere on the board
NUCLEUM_RX: U1.22 (BTLDR_RX/P11); also elsewhere on the board
NUCLEUM_TX: U1.23 (BTLDR_TX/P12); also elsewhere on the board
SCLK: U1.16 (SPI_SCK/P00); also elsewhere on the board

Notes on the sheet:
SPI for commands
DNP
Configured to be normally off. Switch R38/R39 to be normally on.
The UART Lines allow for the NRF to act as a serial slave. This code is provided by nordic and requires rts/cts. We would like to use spi in the futue, then rts and cts will be repurposed as interrupt pins for the spi interface.
